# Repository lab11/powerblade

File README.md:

PowerBlade
==========

PowerBlade is a miniature plug load power meter - it is small enough to fit
between the plug and the outlet while performing its metering operation.
Achieving this form factor requires targeting every aspect of traditional power
meters, including contact method, power supply, voltage and current sensing, and
data communication (Bluetooth Low Energy, in this case).

There have been multiple iterations of PowerBlade, starting with a backscatter-
based variant and eventually transitioning to the BLE version. Along the way
there have been several iterations of the contact method, starting with flexible
PCB layers to touch the prongs and ending with spring-loaded pins which make
contact more reliably and repeatably.

Future work on this system will include improvements to the accuracy of the unit
(PowerBlade readings currently have 5% to 10% error but we believe this can be
significantly lower), as well as safety.

How Do I View My PowerBlade's Data?
-----------------------------------

- **Option 1**: Install [Summon](https://github.com/lab11/summon)
[[Android](https://play.google.com/store/apps/details?id=edu.umich.eecs.lab11.summon&hl=en),
[iOS](https://itunes.apple.com/us/app/summon-lab11/id1051205682?mt=8)].

- **Option 2**: Run a node.js script to view packets on your computer.

    ```sh
    cd data_collection/advertisements/
    npm install
    sudo node powerblade_adv.js
    ```

    This requires that you have support for running as a BLE
    master on your machine. To get setup, see the instructions below.

### BLE and node.js Setup

1. Install [Node.js](https://nodejs.org/en/download/package-manager/) for your platform.
Node.js provides a JavaScript runtime to execute the data collection script in.

2. Install BLE dependencies for your platform.

    - **OS X**: Install [Xcode](https://itunes.apple.com/ca/app/xcode/id497799835?mt=12)
    - **Ubuntu/Debian/Raspbian**:

        ```sh
        sudo apt install bluetooth bluez libbluetooth-dev libudev-dev
        ```

    - **Fedora / Other-RPM based**:

        ```sh
        sudo yum install bluez bluez-libs bluez-libs-devel
        ```

    - **Intel Edison**: See [Configure Intel Edison for Bluetooth LE (Smart) Development](http://rexstjohn.com/configure-intel-edison-for-bluetooth-le-smart-development/)

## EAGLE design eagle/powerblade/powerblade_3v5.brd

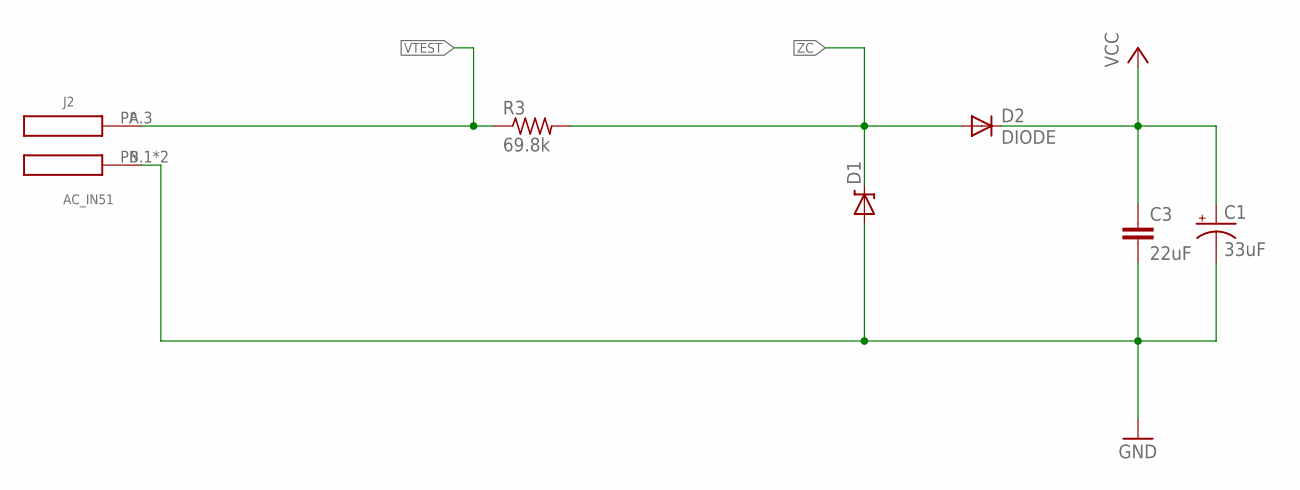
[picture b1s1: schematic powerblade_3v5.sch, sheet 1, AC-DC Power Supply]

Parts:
C1: 33uF; CPOL0805_SM; DIGIKEY 478-8650-1-ND
C3: 22uF; C0603_SM; DIGIKEY 445-9077-1-ND
D1: ZENERBZT52; BZT52; DIGIKEY BZT52C10T-7DICT-ND
D2: DIODE; BAS521
J2: AC_IN51; AC3_51; DIGIKEY ED1649-ND
R3: 69.8k; R1210; DIGIKEY P69.8KAACT-ND

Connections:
GND: C1.-, C3.2, D1.A, J2.PB.1 (N), J2.PB.3 (N); also elsewhere on the board
VCC: C1.+, C3.1, D2.C; also elsewhere on the board
VTEST: J2.PA.3, R3.1; also elsewhere on the board
ZC: D1.C, D2.A, R3.2; also elsewhere on the board

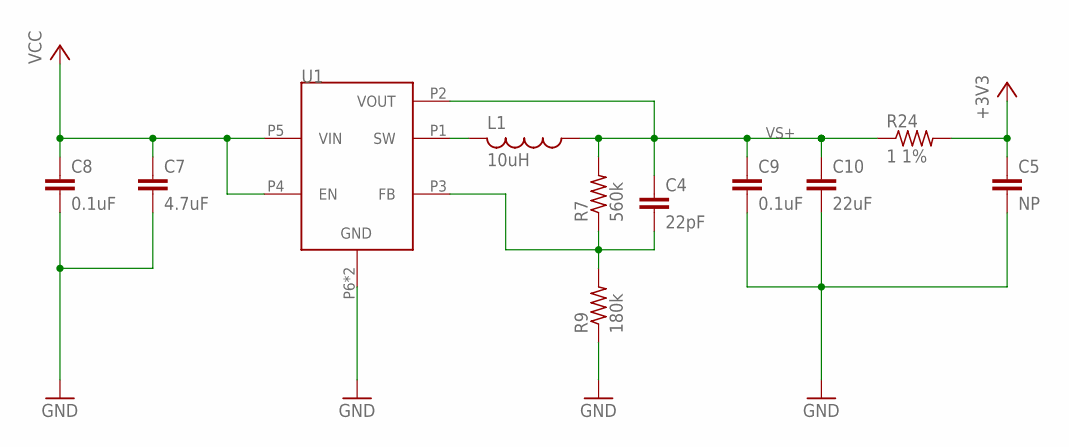
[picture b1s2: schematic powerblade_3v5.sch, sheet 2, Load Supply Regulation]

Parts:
C4: 22pF; C0402; DIGIKEY 445-1239-1-ND
C5: NP; C0603_TN; DIGIKEY NP
C7: 4.7uF; C0402; DIGIKEY 445-8023-1-ND
C8: 0.1uF; C0402; DIGIKEY 445-4952-1-ND
C9: 0.1uF; C0402_SM; DIGIKEY 445-4952-1-ND
C10: 22uF; C0603_SM; DIGIKEY 445-9077-1-ND
L1: 10uH; L0805; DIGIKEY 490-4990-1-ND
R7: 560k; R0402; DIGIKEY P560KLCT-ND
R9: 180k; R0402; DIGIKEY P180KLCT-ND
R24: 1 1%; R0603_SM; DIGIKEY P1.0AJCT-ND
U1: TPS62122; WDFN-6

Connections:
+3V3: C5.1, R24.2; also elsewhere on the board
GND: C5.2, C7.2, C8.2, C9.2, C10.2, R9.1, U1.P6 (GND), U1.PAD (GND); also elsewhere on the board
unnamed: L1.2, U1.P1 (SW)
unnamed: C4.2, R7.1, R9.2, U1.P3 (FB)
VCC: C7.1, C8.1, U1.P4 (EN), U1.P5 (VIN); also elsewhere on the board
VS+: C4.1, C9.1, C10.1, L1.1, R7.2, R24.1, U1.P2 (VOUT)

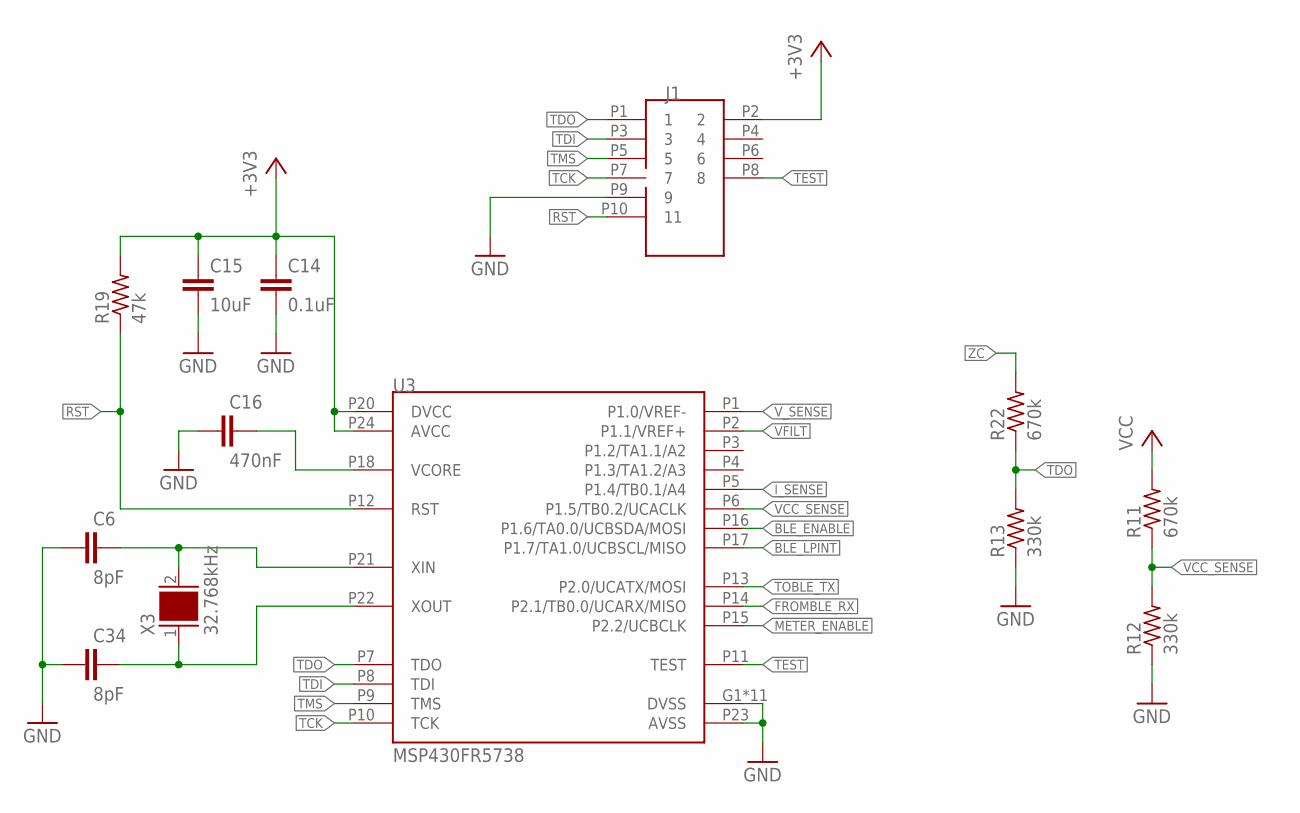
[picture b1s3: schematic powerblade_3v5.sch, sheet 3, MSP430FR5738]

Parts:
C6, C34: 8pF; C0402; DIGIKEY 445-4890-1-ND
C14: 0.1uF; C0402; DIGIKEY 445-4952-1-ND
C15: 10uF; C0603_SM; DIGIKEY 445-6853-1-ND
C16: 470nF; C0402; DIGIKEY 445-4989-1-ND
J1: JTAG_14PIN_IDC-ND; TC2050-IDC-NL-430-ND; DIGIKEY NP
R11, R22: 670k; R0402; DIGIKEY P665KLCT-ND
R12, R13: 330k; R0402; DIGIKEY P330KLCT-ND
R19: 47k; R0402; DIGIKEY P47KJCT-ND
U3: MSP430FR5738; VQFN-24
X3: 32.768kHz; 0805; DIGIKEY 535-12373-1-ND

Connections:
+3V3: C14.1, C15.1, J1.P2 (2), R19.2, U3.P20 (DVCC), U3.P24 (AVCC); also elsewhere on the board
BLE_ENABLE: U3.P16 (P1.6/TA0.0/UCBSDA/MOSI); also elsewhere on the board
BLE_LPINT: U3.P17 (P1.7/TA1.0/UCBSCL/MISO); also elsewhere on the board
FROMBLE_RX: U3.P14 (P2.1/TB0.0/UCARX/MISO); also elsewhere on the board
GND: C6.1, C14.2, C15.2, C16.1, C34.1, J1.P9 (9), R12.1, R13.1, U3.G1 (DVSS), U3.G2 (DVSS), U3.G3 (DVSS), U3.G4 (DVSS), U3.G5 (DVSS), U3.G6 (DVSS), U3.G7 (DVSS), U3.G8 (DVSS), U3.G9 (DVSS), U3.P19 (DVSS), U3.P23 (AVSS), U3.PAD (DVSS); also elsewhere on the board
I_SENSE: U3.P5 (P1.4/TB0.1/A4); also elsewhere on the board
METER_ENABLE: U3.P15 (P2.2/UCBCLK); also elsewhere on the board
unnamed: C34.2, U3.P22 (XOUT), X3.1
unnamed: C16.2, U3.P18 (VCORE)
unnamed: C6.2, U3.P21 (XIN), X3.2
RST: J1.P10 (11), R19.1, U3.P12 (RST)
TCK: J1.P7 (7), U3.P10 (TCK)
TDI: J1.P3 (3), U3.P8 (TDI)
TDO: J1.P1 (1), R13.2, R22.1, U3.P7 (TDO)
TEST: J1.P8 (8), U3.P11 (TEST)
TMS: J1.P5 (5), U3.P9 (TMS)
TOBLE_TX: U3.P13 (P2.0/UCATX/MOSI); also elsewhere on the board
VCC: R11.2; also elsewhere on the board
VCC_SENSE: R11.1, R12.2, U3.P6 (P1.5/TB0.2/UCACLK)
VFILT: U3.P2 (P1.1/VREF+); also elsewhere on the board
V_SENSE: U3.P1 (P1.0/VREF-); also elsewhere on the board
ZC: R22.2; also elsewhere on the board

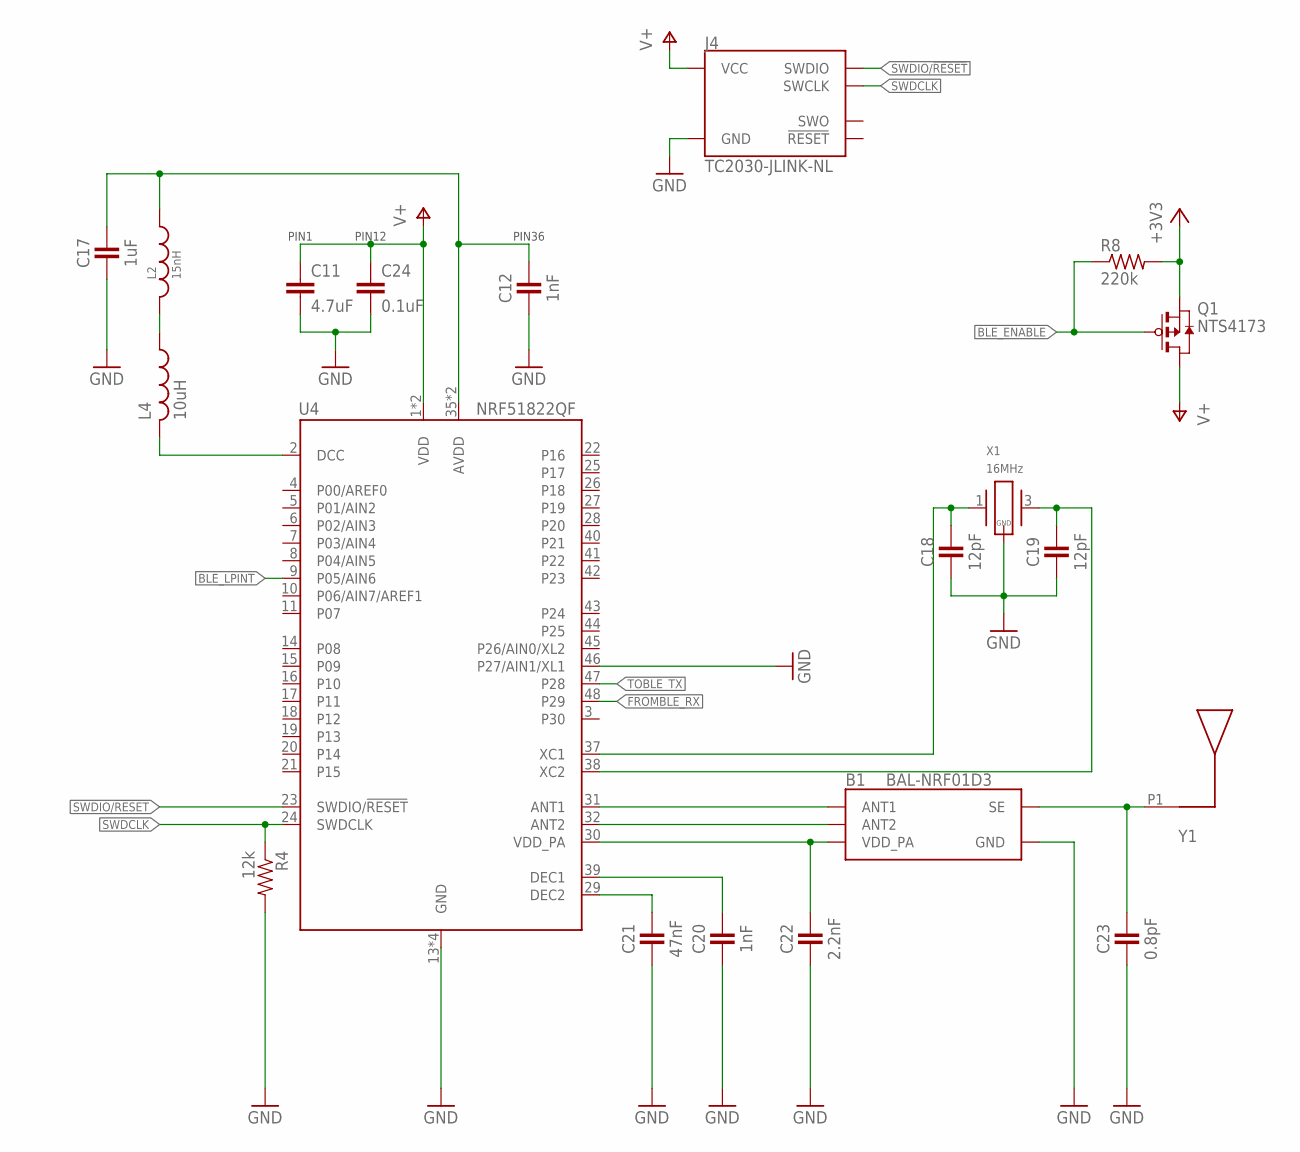
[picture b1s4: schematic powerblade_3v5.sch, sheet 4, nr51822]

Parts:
B1: BAL-NRF01D3
C11: 4.7uF; C0402; DIGIKEY 445-5947-1-ND
C12, C20: 1nF; 0402_CAP; DIGIKEY 490-1303-1-ND
C17: 1uF; 0402_CAP; DIGIKEY 1276-1513-1-ND
C18, C19: 12pF; 0402_CAP; DIGIKEY 490-6197-1-ND
C21: 47nF; 0402_CAP; DIGIKEY 445-1264-1-ND
C22: 2.2nF; 0402_CAP; DIGIKEY 490-5419-1-ND
C23: 0.8pF; 0402_CAP; DIGIKEY 490-6269-1-ND
C24: 0.1uF; C0402; DIGIKEY 445-4952-1-ND
J4: TC2030-JLINK-NL; TC2030-IDC-NL; DIGIKEY NP
L2: 15nH; 0402_CAP; DIGIKEY 587-1521-1-ND
L4: 10uH; C0603_TN; DIGIKEY 490-4025-1-ND
Q1: NTS4173; SC-70-3
R4: 12k; 0402_RES; DIGIKEY RHM12.0KCDCT-ND
R8: 220k; R0402_SM; DIGIKEY P220KJCT-ND
U4: NRF51822QF; QFN-48-6MM
X1: 16MHz; TXC-8Y; DIGIKEY 887-2003-1-ND
Y1: UREACH_XTEND

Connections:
+3V3: Q1.P2 (S), R8.2; also elsewhere on the board
AVDD: C12.1, C17.1, L2.1, U4.35 (AVDD), U4.36 (AVDD)
BLE_ENABLE: Q1.P1 (G), R8.1; also elsewhere on the board
BLE_LPINT: U4.9 (P05/AIN6); also elsewhere on the board
DCC: L4.2, U4.2 (DCC)
FROMBLE_RX: U4.48 (P29); also elsewhere on the board
GND: B1.GND, C11.2, C12.2, C17.2, C18.2, C19.2, C20.2, C21.2, C22.2, C23.2, C24.2, J4.5 (GND), R4.2, U4.13 (GND), U4.33 (GND), U4.34 (GND), U4.46 (P27/AIN1/XL1), U4.GND, X1.2 (GND), X1.4 (GND); also elsewhere on the board
unnamed: B1.SE, C23.1, Y1.P1
unnamed: B1.ANT1, U4.31 (ANT1)
unnamed: B1.ANT2, U4.32 (ANT2)
unnamed: L2.2, L4.1
unnamed: C18.1, U4.37 (XC1), X1.1
unnamed: C19.1, U4.38 (XC2), X1.3 (2)
unnamed: C20.1, U4.39 (DEC1)
unnamed: C21.1, U4.29 (DEC2)
SWDCLK: J4.4 (SWCLK), R4.1, U4.24 (SWDCLK)
SWDIO/!RESET: J4.2 (SWDIO), U4.23 (SWDIO/!RESET)
TOBLE_TX: U4.47 (P28); also elsewhere on the board
V+: C11.1, C24.1, J4.1 (VCC), Q1.P3 (D), U4.1 (VDD), U4.12 (VDD)
VDD_PA: B1.VCC (VDD_PA), C22.1, U4.30 (VDD_PA)

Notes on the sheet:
PIN12
PIN1
PIN36

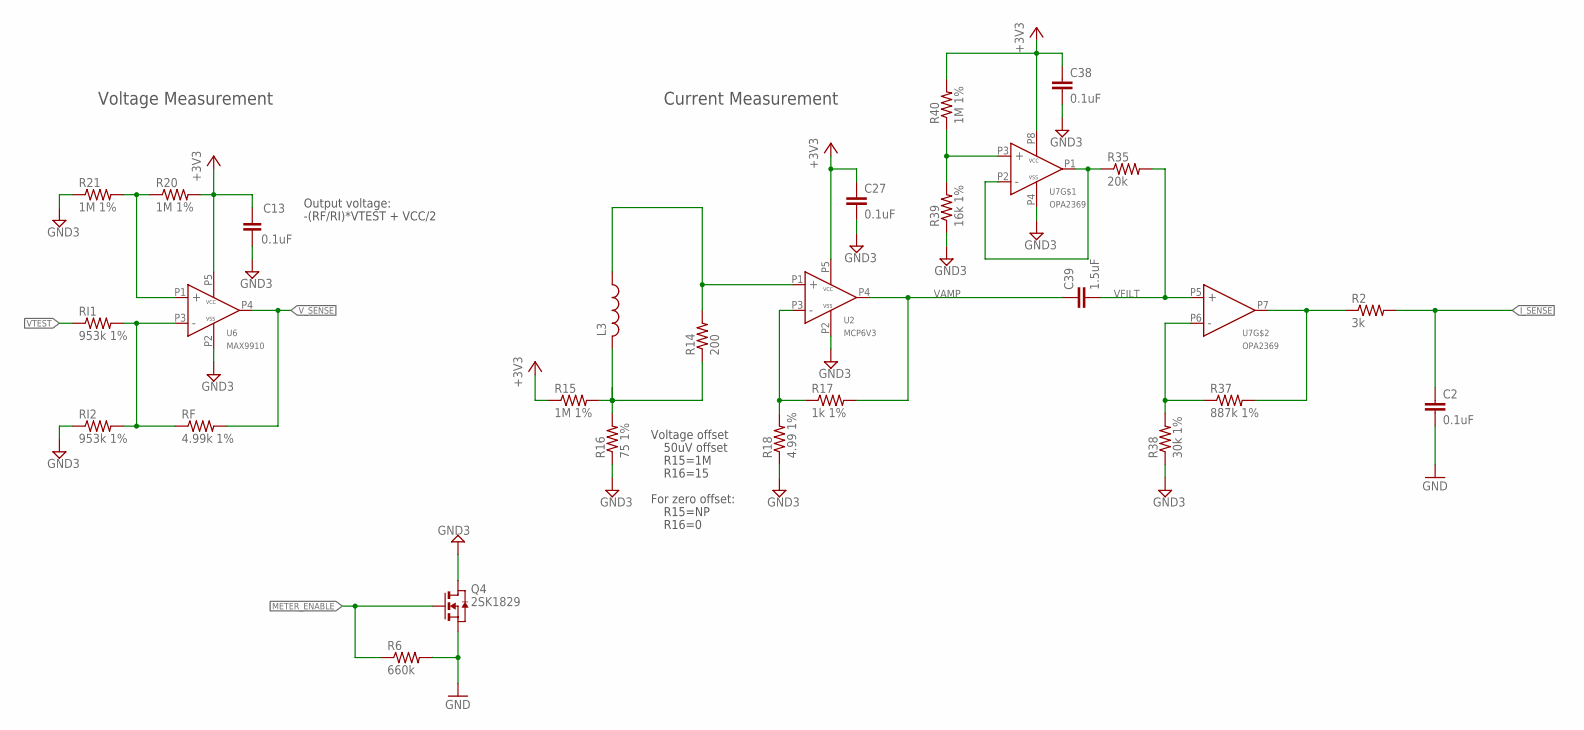
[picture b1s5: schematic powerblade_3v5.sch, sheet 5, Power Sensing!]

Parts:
C2: 0.1uF; C0402; DIGIKEY 490-10777-1-ND
C13: 0.1uF; 0402_CAP; DIGIKEY 445-4952-1-ND
C27, C38: 0.1uF; C0402; DIGIKEY 445-4952-1-ND
C39: 1.5uF; C0402; DIGIKEY 445-13815-1-ND
L3: L-USL0805; L0805; DIGIKEY 732-3452-1-ND
Q4: 2SK1829; SC-70-3
R2: 3k; R0402_SM; DIGIKEY P3.00KLCT-ND
R6: 660k; R0402; DIGIKEY P665KLCT-ND
R14: 200; R0402; DIGIKEY P200LCT-ND
R15, R20, R40: 1M 1%; R0402; DIGIKEY P1.00MLCT-ND
R16: 75 1%; R0402; DIGIKEY P75.0LCT-ND
R17: 1k 1%; R0402; DIGIKEY P1.00KLCT-ND
R18: 4.99 1%; R0402; DIGIKEY RMCF0402FT4R99CT-ND
R21: 1M 1%; R0402_SM; DIGIKEY P1.00MLCT-ND
R35: 20k; R0402; DIGIKEY P20.0KLCT-ND
R37: 887k 1%; R0402; DIGIKEY P887KLCT-ND
R38: 30k 1%; R0402; DIGIKEY P30.0KLCT-ND
R39: 16k 1%; R0402; DIGIKEY P16.0KLCT-ND
RF: 4.99k 1%; R0402; DIGIKEY P4.99KLCT-ND
RI1, RI2: 953k 1%; R0402; DIGIKEY P953KLCT-ND
U2: MCP6V3; SC70-5; DIGIKEY 296-19547-1-ND
U6: MAX9910; SC70-5; DIGIKEY 296-25252-1-ND
U7: OPA2369; SOT-23-8

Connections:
+3V3: C13.1, C27.1, C38.1, R15.1, R20.2, R40.2, U2.P5 (VCC), U6.P5 (VCC), U7.P8 (VCC); also elsewhere on the board
GND: C2.2, Q4.P2 (S), R6.2; also elsewhere on the board
GND3: C13.2, C27.2, C38.2, Q4.P3 (D), R16.1, R18.1, R21.1, R38.1, R39.1, RI2.1, U2.P2 (VSS), U6.P2 (VSS), U7.P4 (VSS)
I_SENSE: C2.1, R2.2; also elsewhere on the board
METER_ENABLE: Q4.P1 (G), R6.1; also elsewhere on the board
unnamed: R2.1, R37.2, U7.P7 (OUT)
unnamed: L3.2, R14.1, R15.2, R16.2
unnamed: L3.1, R14.2, U2.P1 (IN+)
unnamed: R20.1, R21.2, U6.P1 (IN+)
unnamed: RF.1, RI1.2, RI2.2, U6.P3 (IN-)
unnamed: R17.1, R18.2, U2.P3 (IN-)
unnamed: R37.1, R38.2, U7.P6 (IN-)
unnamed: R35.1, U7.P1 (OUT), U7.P2 (IN-)
unnamed: R39.2, R40.1, U7.P3 (IN+)
VAMP: C39.1, R17.2, U2.P4 (OUT)
VFILT: C39.2, R35.2, U7.P5 (IN+); also elsewhere on the board
VTEST: RI1.1; also elsewhere on the board
V_SENSE: RF.2, U6.P4 (OUT); also elsewhere on the board

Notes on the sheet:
Voltage offset
50uV offset
For zero offset:
R15=NP
R16=0
Current Measurement
Voltage Measurement
Output voltage:
-(RF/RI)*VTEST + VCC/2
R15=1M
R16=15

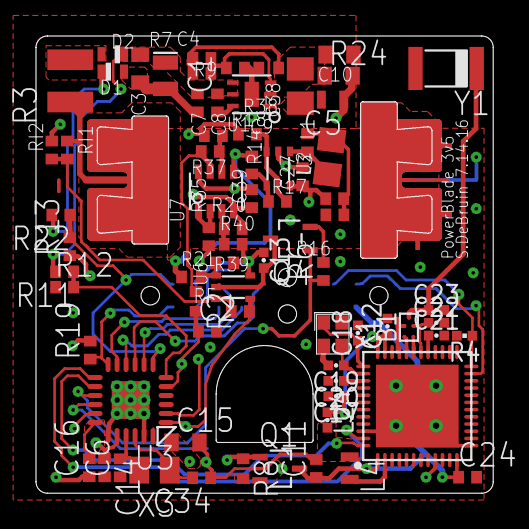
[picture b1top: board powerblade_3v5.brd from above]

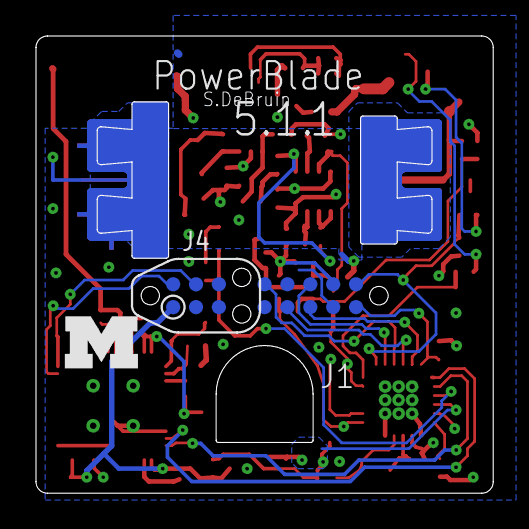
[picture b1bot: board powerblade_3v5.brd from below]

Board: 4 copper layers, 25.4 x 25.4 mm, 78 parts (3 on the bottom side), 51 nets.

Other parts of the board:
U$1: BLOCK-M

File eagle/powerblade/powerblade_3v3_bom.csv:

"Part";"Value";"Device";"Package";"Description";"DIGIKEY";"DIGIKEY_2";"DIGIKEY_3";"DIGIKEY_4";"FRACTUS";"MOUSER";
"B1";"BAL-NRF01D3";"BAL-NRF01D3";"BAL-NRF01D3";"50 ohm nominal input / conjugate match balun to nRF51422-QFAA,";"497-13637-1-ND";"";"";"";"";"511-BAL-NRF01D3";
"C1";"33uF";"CPOL-US0805_SM";"CPOL0805_SM";"POLARIZED CAPACITOR, American symbol";"478-8650-1-ND";"";"";"";"";"";
"C2";"0.1uF";"C-EUC0402";"C0402";"CAPACITOR, European symbol";"490-10777-1-ND";"";"";"";"";"";
"C3";"22uF";"C-EUC0603_SM";"C0603_SM";"CAPACITOR, European symbol";"445-9077-1-ND";"";"";"";"";"";
"C4";"22pF";"C-EUC0402";"C0402";"CAPACITOR, European symbol";"445-1239-1-ND";"";"";"";"";"";
"C5";"NP";"C-EUC0603_TN";"C0603_TN";"CAPACITOR, European symbol";"NP";"";"";"";"";"";
"C6";"8pF";"C-EUC0402";"C0402";"CAPACITOR, European symbol";"445-4890-1-ND";"";"";"";"";"";
"C7";"4.7uF";"C-EUC0402";"C0402";"CAPACITOR, European symbol";"445-8023-1-ND";"";"";"";"";"";
"C8";"0.1uF";"C-EUC0402";"C0402";"CAPACITOR, European symbol";"445-4952-1-ND";"";"";"";"";"";
"C9";"0.1uF";"C-EUC0402_SM";"C0402_SM";"CAPACITOR, European symbol";"445-4952-1-ND";"";"";"";"";"";
"C10";"22uF";"C-EUC0603_SM";"C0603_SM";"CAPACITOR, European symbol";"445-9077-1-ND";"";"";"";"";"";
"C11";"4.7uF";"C-EUC0402";"C0402";"CAPACITOR, European symbol";"445-5947-1-ND";"";"";"";"";"";
"C12";"1nF";"CAPACITOR";"0402_CAP";"0402 Capacitor";"490-1303-1-ND";"";"";"";"";"";
"C13";"0.1uF";"CAPACITOR";"0402_CAP";"0402 Capacitor";"445-4952-1-ND";"";"";"";"";"";
"C14";"0.1uF";"C-EUC0402";"C0402";"CAPACITOR, European symbol";"445-4952-1-ND";"";"";"";"";"";
"C15";"10uF";"C-EUC0603_SM";"C0603_SM";"CAPACITOR, European symbol";"445-6853-1-ND";"";"";"";"";"";
"C16";"470nF";"C-EUC0402";"C0402";"CAPACITOR, European symbol";"445-4989-1-ND";"";"";"";"";"";
"C17";"1uF";"CAPACITOR";"0402_CAP";"0402 Capacitor";"1276-1513-1-ND";"";"";"";"";"";
"C18";"12pF";"CAPACITOR";"0402_CAP";"0402 Capacitor";"490-6197-1-ND";"";"";"";"";"";
"C19";"12pF";"CAPACITOR";"0402_CAP";"0402 Capacitor";"490-6197-1-ND";"";"";"";"";"";
"C20";"1nF";"CAPACITOR";"0402_CAP";"0402 Capacitor";"490-1303-1-ND";"";"";"";"";"";
"C21";"47nF";"CAPACITOR";"0402_CAP";"0402 Capacitor";"445-1264-1-ND";"";"";"";"";"";
"C22";"2.2nF";"CAPACITOR";"0402_CAP";"0402 Capacitor";"490-5419-1-ND";"";"";"";"";"";
"C23";"0.8pF";"CAPACITOR";"0402_CAP";"0402 Capacitor";"490-6269-1-ND";"";"";"";"";"";
"C24";"0.1uF";"C-EUC0402";"C0402";"CAPACITOR, European symbol";"445-4952-1-ND";"";"";"";"";"";
"C27";"0.1uF";"C-EUC0402";"C0402";"CAPACITOR, European symbol";"445-4952-1-ND";"";"";"";"";"";
"C34";"8pF";"C-EUC0402";"C0402";"CAPACITOR, European symbol";"445-4890-1-ND";"";"";"";"";"";
"C38";"0.1uF";"C-EUC0402";"C0402";"CAPACITOR, European symbol";"445-4952-1-ND";"";"";"";"";"";
"C39";"1.5uF";"C-EUC0402";"C0402";"CAPACITOR, European symbol";"445-13815-1-ND";"";"";"";"";"";
"D1";"ZENERBZT52";"ZENERBZT52";"BZT52";"";"BZT52C10T-7DICT-ND ";"";"";"";"";"";
"D2";"DIODE";"DIODE";"BAS521";"";"BAS521-7DICT-ND";"";"";"";"";"";
"J1";"JTAG_14PIN_IDC-ND";"JTAG_14PIN_IDC-ND";"TC2050-IDC-NL-430-ND";"";"NP";"";"";"";"";"";
"J2";"AC_INF45";"AC_INF45";"AC3_F45";"";"ED1649-ND";"ED1649-ND";"ED1649-ND";"ED1649-ND";"";"";
"J4";"TC2030-JLINK-NL";"TC2030-JLINK-NL";"TC2030-IDC-NL";"";"NP";"";"";"";"";"";
"L1";"10uH";"L-USL0805";"L0805";"INDUCTOR, American symbol";"490-4990-1-ND";"";"";"";"";"";
"L2";"15nH";"INDUCTOR0402";"0402_CAP";"";"587-1521-1-ND";"";"";"";"";"";
"L3";"";"L-USL0805";"L0805";"INDUCTOR, American symbol";"732-3452-1-ND";"";"";"";"";"";
"L4";"10uH";"L-USL0603_TN";"C0603_TN";"INDUCTOR, American symbol";"490-4025-1-ND";"";"";"";"";"";
"Q1";"NTS4173";"NTS4173";"SC-70-3";"";"NTS4173PT1GOSCT-ND";"";"";"";"";"";
"Q4";"2SK1829";"2SK1829";"SC-70-3";"";"2SK1829TE85LFCT-ND";"";"";"";"";"";
"R2";"3k";"R-US_R0402_SM";"R0402_SM";"RESISTOR, American symbol";"P3.00KLCT-ND";"";"";"";"";"";
"R3";"69.8k";"R-US_R1210";"R1210";"RESISTOR, American symbol";"P69.8KAACT-ND";"";"";"";"";"";
"R4";"12k";"RESISTOR";"0402_RES";"Resistor";"RHM12.0KCDCT-ND";"";"";"";"";"";
"R6";"660k";"R-US_R0402";"R0402";"RESISTOR, American symbol";"P665KLCT-ND";"";"";"";"";"";
"R7";"560k";"R-US_R0402";"R0402";"RESISTOR, American symbol";"P560KLCT-ND";"";"";"";"";"";
"R8";"220k";"R-US_R0402_SM";"R0402_SM";"RESISTOR, American symbol";"P220KJCT-ND";"";"";"";"";"";
"R9";"180k";"R-US_R0402";"R0402";"RESISTOR, American symbol";"P180KLCT-ND";"";"";"";"";"";
"R11";"670k";"R-US_R0402";"R0402";"RESISTOR, American symbol";"P665KLCT-ND";"";"";"";"";"";
"R12";"330k";"R-US_R0402";"R0402";"RESISTOR, American symbol";"P330KLCT-ND";"";"";"";"";"";
"R13";"330k";"R-US_R0402";"R0402";"RESISTOR, American symbol";"P330KLCT-ND";"";"";"";"";"";
"R14";"200";"R-US_R0402";"R0402";"RESISTOR, American symbol";"P200LCT-ND";"";"";"";"";"";
"R15";"1M 1%";"R-US_R0402";"R0402";"RESISTOR, American symbol";"P1.00MLCT-ND";"";"";"";"";"";
"R16";"75 1%";"R-US_R0402";"R0402";"RESISTOR, American symbol";"P75.0LCT-ND";"";"";"";"";"";
"R17";"1k 1%";"R-US_R0402";"R0402";"RESISTOR, American symbol";"P1.00KLCT-ND";"";"";"";"";"";
"R18";"4.99 1%";"R-US_R0402";"R0402";"RESISTOR, American symbol";"RMCF0402FT4R99CT-ND";"";"";"";"";"";
"R19";"47k";"R-US_R0402";"R0402";"RESISTOR, American symbol";"P47KJCT-ND";"";"";"";"";"";
"R20";"1M 1%";"R-US_R0402";"R0402";"RESISTOR, American symbol";"P1.00MLCT-ND";"";"";"";"";"";
"R21";"1M 1%";"R-US_R0402_SM";"R0402_SM";"RESISTOR, American symbol";"P1.00MLCT-ND";"";"";"";"";"";
"R22";"670k";"R-US_R0402";"R0402";"RESISTOR, American symbol";"P665KLCT-ND";"";"";"";"";"";
"R24";"1 1%";"R-US_R0603_SM";"R0603_SM";"RESISTOR, American symbol";"P1.0AJCT-ND";"";"";"";"";"";
"R35";"20k";"R-US_R0402";"R0402";"RESISTOR, American symbol";"P20.0KLCT-ND";"";"";"";"";"";
"R37";"887k 1%";"R-US_R0402";"R0402";"RESISTOR, American symbol";"P887KLCT-ND";"";"";"";"";"";
"R38";"30k 1%";"R-US_R0402";"R0402";"RESISTOR, American symbol";"P30.0KLCT-ND";"";"";"";"";"";
"R39";"16k 1%";"R-US_R0402";"R0402";"RESISTOR, American symbol";"P16.0KLCT-ND";"";"";"";"";"";
"R40";"1M 1%";"R-US_R0402";"R0402";"RESISTOR, American symbol";"P1.00MLCT-ND";"";"";"";"";"";
"RF";"4.99k 1%";"R-US_R0402";"R0402";"RESISTOR, American symbol";"P4.99KLCT-ND";"";"";"";"";"";
"RI1";"953k 1%";"R-US_R0402";"R0402";"RESISTOR, American symbol";"P953KLCT-ND";"";"";"";"";"";
"RI2";"953k 1%";"R-US_R0402";"R0402";"RESISTOR, American symbol";"P953KLCT-ND";"";"";"";"";"";
"SV1";"";"MA12-11M27";"MA12-1_1MM27";"PIN HEADER";"S9014E-12-ND";"";"";"";"";"";
"U1";"TPS62122";"TPS62122";"WDFN-6";"";"296-27695-1-ND";"";"";"";"";"";
"U2";"MCP6V3";"MCP6V3";"SC70-5";"";"296-19547-1-ND";"";"";"";"";"";
"U3";"MSP430FR5738";"MSP430FR5738";"VQFN-24";"";"296-29232-1-ND";"";"";"";"";"";
"U4";"NRF51822QF";"NRF51822QF";"QFN-48-6MM";"Multiprotocol Bluetooth® 4.0 low energy/2.4 GHz RF SoC";"1490-1032-1-ND";"";"";"";"";"949-NRF51822-QFAB-R7";
"U6";"MAX9910";"MAX9910";"SC70-5";"";"296-25252-1-ND";"";"";"";"";"";
"U7";"OPA2369";"OPA2369";"SOT-23-8";"";"296-22671-1-ND";"";"";"";"";"";
"X1";"16MHz";"TXC-8Y";"TXC-8Y";"2mmx1.6mm SMD Crystal";"887-2003-1-ND";"";"";"";"";"";
"X3";"32.768kHz";"CRYSTAL_0805";"0805";"";"535-12373-1-ND";"";"";"";"";"";
"Y1";"UREACH_XTEND";"UREACH_XTEND";"UREACH_XTEND";"";"";"";"";"";"FR05-S1-N-0-110";"";

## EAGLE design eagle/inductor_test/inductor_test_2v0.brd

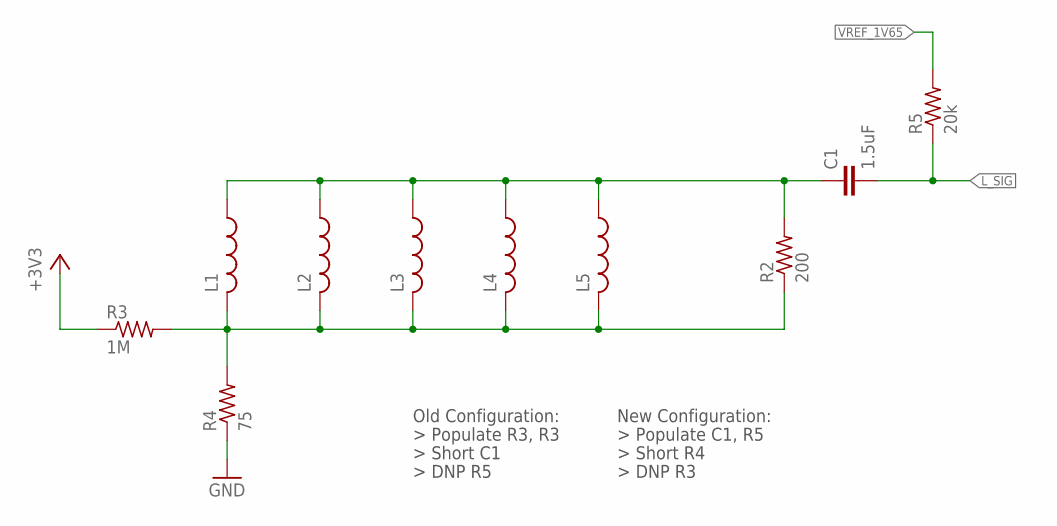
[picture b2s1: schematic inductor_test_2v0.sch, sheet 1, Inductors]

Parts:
C1: 1.5uF; C0402; DIGIKEY 445-13815-1-ND
L1, L2, L3, L4, L5: L-USL0805; L0805; DIGIKEY 732-3452-1-ND
R2: 200; R0402; DIGIKEY P200LCT-ND
R3: 1M; R0402; DIGIKEY P1.00MLCT-ND
R4: 75; R0402; DIGIKEY P75.0LCT-ND
R5: 20k; R0402; DIGIKEY P20.0KLCT-ND

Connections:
+3V3: R3.1; also elsewhere on the board
GND: R4.1; also elsewhere on the board
L1P2: L1.2, L2.2, L3.2, L4.2, L5.2, R2.1, R3.2, R4.2
L_SIG: C1.2, R5.1; also elsewhere on the board
unnamed: C1.1, L1.1, L2.1, L3.1, L4.1, L5.1, R2.2
VREF_1V65: R5.2; also elsewhere on the board

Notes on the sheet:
Old Configuration:
New Configuration:

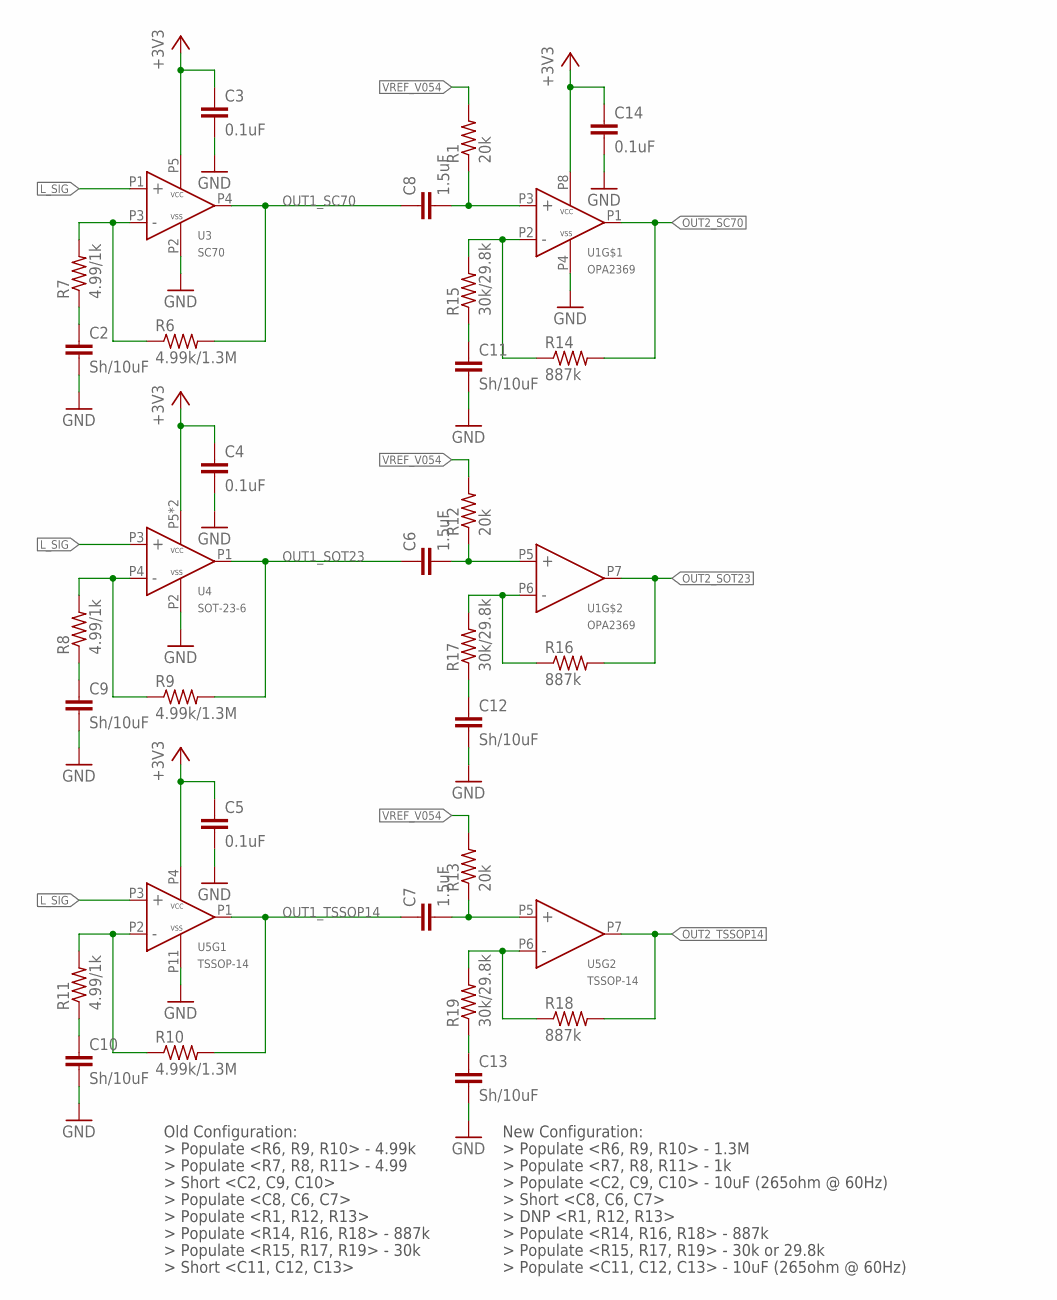
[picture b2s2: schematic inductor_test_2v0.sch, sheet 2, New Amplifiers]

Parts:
C2, C9, C10, C11, C12, C13: Sh/10uF; C0402; DIGIKEY 1276-1450-1-ND
C3, C4, C5, C14: 0.1uF; C0402; DIGIKEY 445-4952-1-ND
C6, C7, C8: 1.5uF; C0402; DIGIKEY 445-13815-1-ND
R1, R12, R13: 20k; R0402; DIGIKEY P20.0KLCT-ND
R6, R9, R10: 4.99k/1.3M; R0402; DIGIKEY P4.99KLCT-ND
R7, R8, R11: 4.99/1k; R0402; DIGIKEY RMCF0402FT4R99CT-ND
R14, R16, R18: 887k; R0402; DIGIKEY P887KLCT-ND
R15, R17, R19: 30k/29.8k; R0402; DIGIKEY P30.0KLCT-ND
U1: OPA2369; SOT-23-8
U3: SC70; SC70-5; DIGIKEY 296-22191-1-ND
U4: SOT-23-6
U5: TSSOP-14

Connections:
+3V3: C3.1, C4.1, C5.1, C14.1, U1.P8 (VCC), U3.P5 (VCC), U4.P5 (VCC), U4.P6 (VCC), U5.P4 (VCC); also elsewhere on the board
GND: C2.2, C3.2, C4.2, C5.2, C9.2, C10.2, C11.2, C12.2, C13.2, C14.2, U1.P4 (VSS), U3.P2 (VSS), U4.P2 (VSS), U5.P11 (VSS); also elsewhere on the board
L_SIG: U3.P1 (IN+), U4.P3 (IN+), U5.P3 (IN+); also elsewhere on the board
unnamed: C10.1, R11.1
unnamed: C9.1, R8.1
unnamed: R6.1, R7.2, U3.P3 (IN-)
unnamed: R8.2, R9.1, U4.P4 (IN-)
unnamed: C2.1, R7.1
unnamed: C8.2, R1.1, U1.P3 (IN+)
unnamed: R10.1, R11.2, U5.P2 (IN-)
unnamed: R14.1, R15.2, U1.P2 (IN-)
unnamed: C6.2, R12.1, U1.P5 (IN+)
unnamed: C11.1, R15.1
unnamed: C7.2, R13.1, U5.P5 (IN+)
unnamed: R16.1, R17.2, U1.P6 (IN-)
unnamed: C12.1, R17.1
unnamed: R18.1, R19.2, U5.P6 (IN-)
unnamed: C13.1, R19.1
OUT1_SC70: C8.1, R6.2, U3.P4 (OUT); also elsewhere on the board
OUT1_SOT23: C6.1, R9.2, U4.P1 (OUT); also elsewhere on the board
OUT1_TSSOP14: C7.1, R10.2, U5.P1 (OUT); also elsewhere on the board
OUT2_SC70: R14.2, U1.P1 (OUT); also elsewhere on the board
OUT2_SOT23: R16.2, U1.P7 (OUT); also elsewhere on the board
OUT2_TSSOP14: R18.2, U5.P7 (OUT); also elsewhere on the board
VREF_V054: R1.2, R12.2, R13.2; also elsewhere on the board

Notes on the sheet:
Old Configuration:
New Configuration:

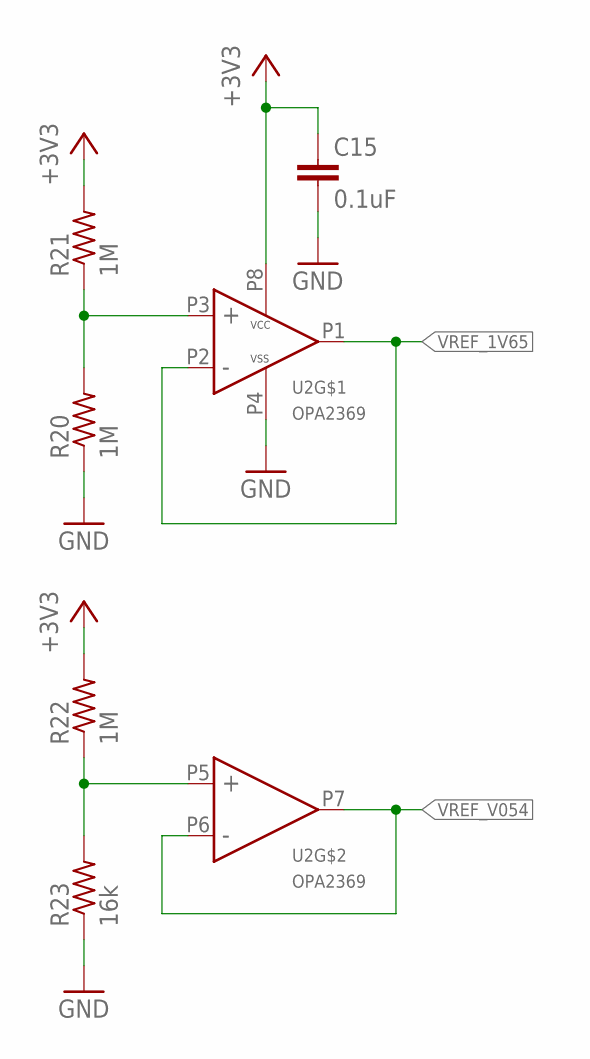
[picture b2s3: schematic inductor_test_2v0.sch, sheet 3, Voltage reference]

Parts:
C15: 0.1uF; C0402; DIGIKEY 445-4952-1-ND
R20, R21, R22: 1M; R0402; DIGIKEY P1.00MLCT-ND
R23: 16k; R0402; DIGIKEY P16.0KLCT-ND
U2: OPA2369; SOT-23-8

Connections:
+3V3: C15.1, R21.2, R22.2, U2.P8 (VCC); also elsewhere on the board
GND: C15.2, R20.1, R23.1, U2.P4 (VSS); also elsewhere on the board
unnamed: R22.1, R23.2, U2.P5 (IN+)
unnamed: R20.2, R21.1, U2.P3 (IN+)
VREF_1V65: U2.P1 (OUT), U2.P2 (IN-); also elsewhere on the board
VREF_V054: U2.P6 (IN-), U2.P7 (OUT); also elsewhere on the board

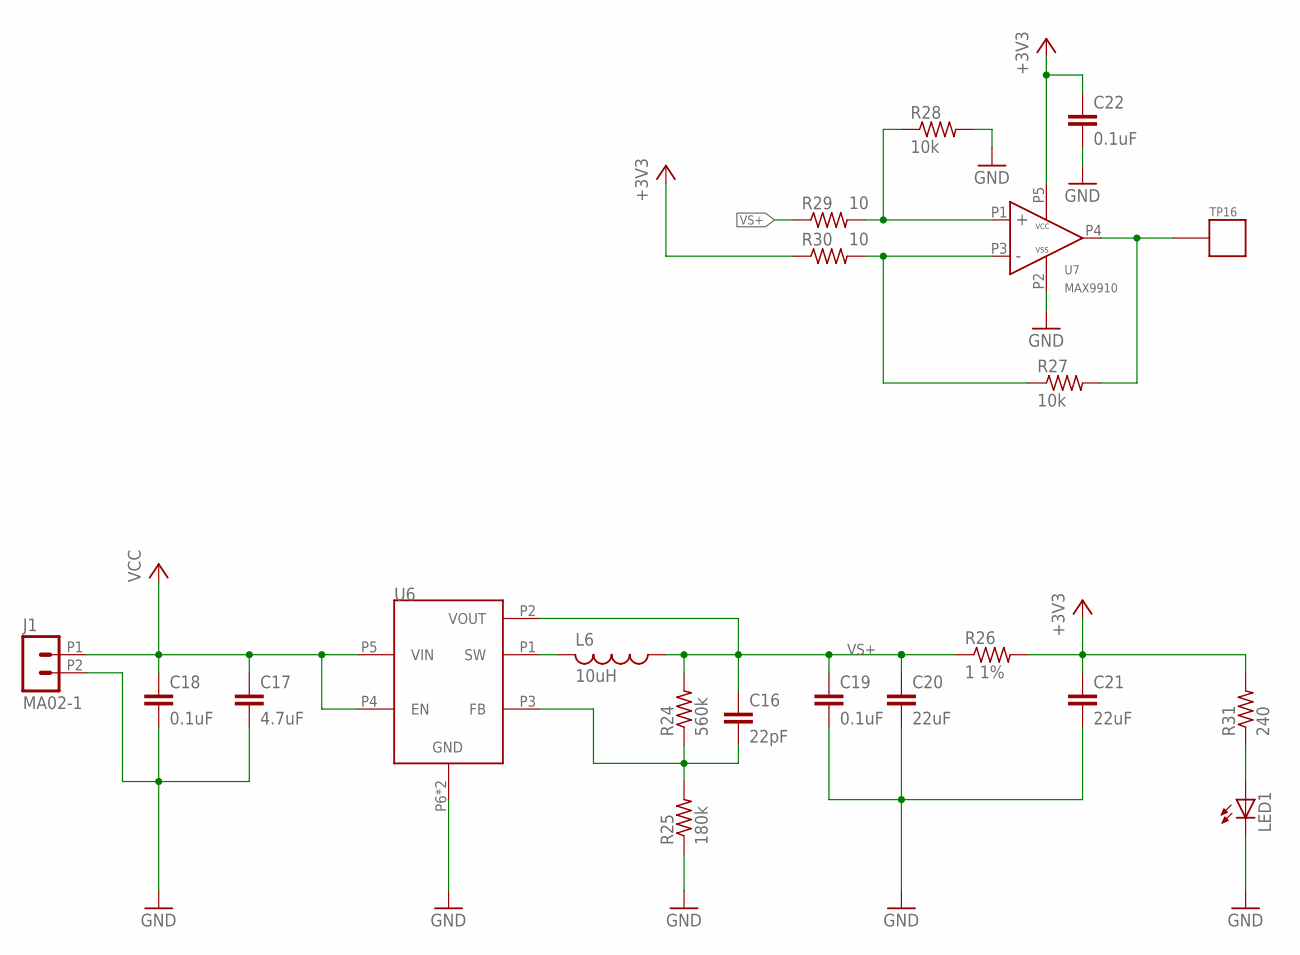
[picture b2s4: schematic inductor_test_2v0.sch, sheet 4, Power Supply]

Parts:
C16: 22pF; C0402_SM; DIGIKEY 445-1239-1-ND
C17: 4.7uF; C0402_SM; DIGIKEY 445-8023-1-ND
C18, C19: 0.1uF; C0402_SM; DIGIKEY 445-4952-1-ND
C20, C21: 22uF; C0603_SM; DIGIKEY 445-9077-1-ND
C22: 0.1uF; C0603; DIGIKEY 445-4952-1-ND
J1: MA02-1; MA02-1_MOLEX-TH
L6: 10uH; L0805; DIGIKEY 490-4990-1-ND
LED1: LED3MM; DIGIKEY 1125-1181-ND
R24: 560k; R0402_SM; DIGIKEY P560KLCT-ND
R25: 180k; R0402_SM; DIGIKEY P180KLCT-ND
R26: 1 1%; R0603_SM; DIGIKEY P1.0AJCT-ND
R27, R28: 10k; R0603; DIGIKEY P10KGCT-ND
R29, R30: 10; R0603; DIGIKEY P10GCT-ND
R31: 240; R0603; DIGIKEY P240GCT-ND
TP16: TP_MULT; DIGIKEY 36-5013-ND
U6: TPS62122; WDFN-6
U7: MAX9910; SC70-5

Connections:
+3V3: C21.1, C22.1, R26.2, R30.1, R31.2, U7.P5 (VCC); also elsewhere on the board
GND: C17.2, C18.2, C19.2, C20.2, C21.2, C22.2, J1.P2 (2), LED1.K (C), R25.1, R28.2, U6.P6 (GND), U6.PAD (GND), U7.P2 (VSS); also elsewhere on the board
unnamed: C16.2, R24.1, R25.2, U6.P3 (FB)
unnamed: L6.2, U6.P1 (SW)
unnamed: R28.1, R29.2, U7.P1 (IN+)
unnamed: R27.1, R30.2, U7.P3 (IN-)
unnamed: R27.2, TP16.P$1, U7.P4 (OUT)
unnamed: LED1.A, R31.1
VCC: C17.1, C18.1, J1.P1 (1), U6.P4 (EN), U6.P5 (VIN)
VS+: C16.1, C19.1, C20.1, L6.1, R24.2, R26.1, R29.1, U6.P2 (VOUT)

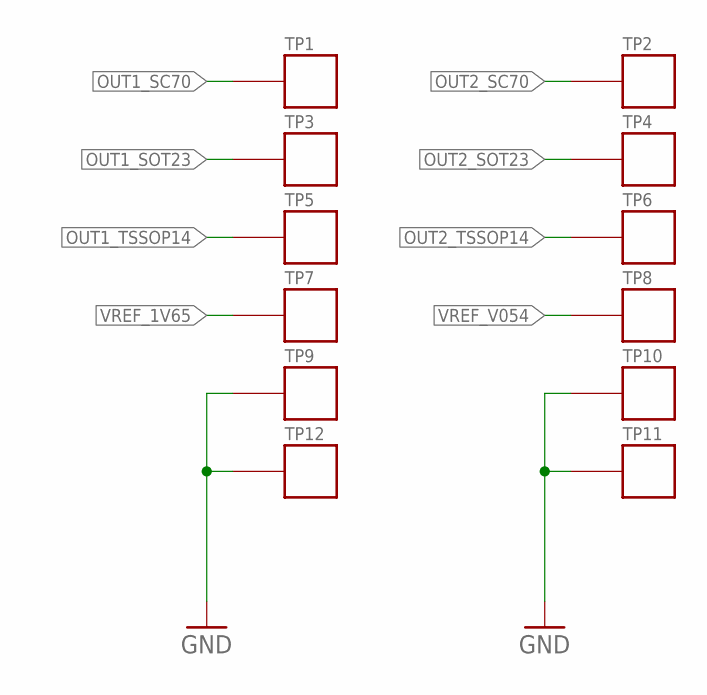
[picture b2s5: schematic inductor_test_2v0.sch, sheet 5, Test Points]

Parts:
TP1, TP2: TP_MULT; DIGIKEY 36-5126-ND
TP3, TP4: TP_MULT; DIGIKEY 36-5128-ND
TP5, TP6: TP_MULT; DIGIKEY 36-5014-ND
TP7, TP8: TP_MULT; DIGIKEY 36-5010-ND
TP9, TP10, TP11, TP12: TP_MULT; DIGIKEY 36-5011-ND

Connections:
GND: TP9.P$1, TP10.P$1, TP11.P$1, TP12.P$1; also elsewhere on the board
OUT1_SC70: TP1.P$1; also elsewhere on the board
OUT1_SOT23: TP3.P$1; also elsewhere on the board
OUT1_TSSOP14: TP5.P$1; also elsewhere on the board
OUT2_SC70: TP2.P$1; also elsewhere on the board
OUT2_SOT23: TP4.P$1; also elsewhere on the board
OUT2_TSSOP14: TP6.P$1; also elsewhere on the board
VREF_1V65: TP7.P$1; also elsewhere on the board
VREF_V054: TP8.P$1; also elsewhere on the board

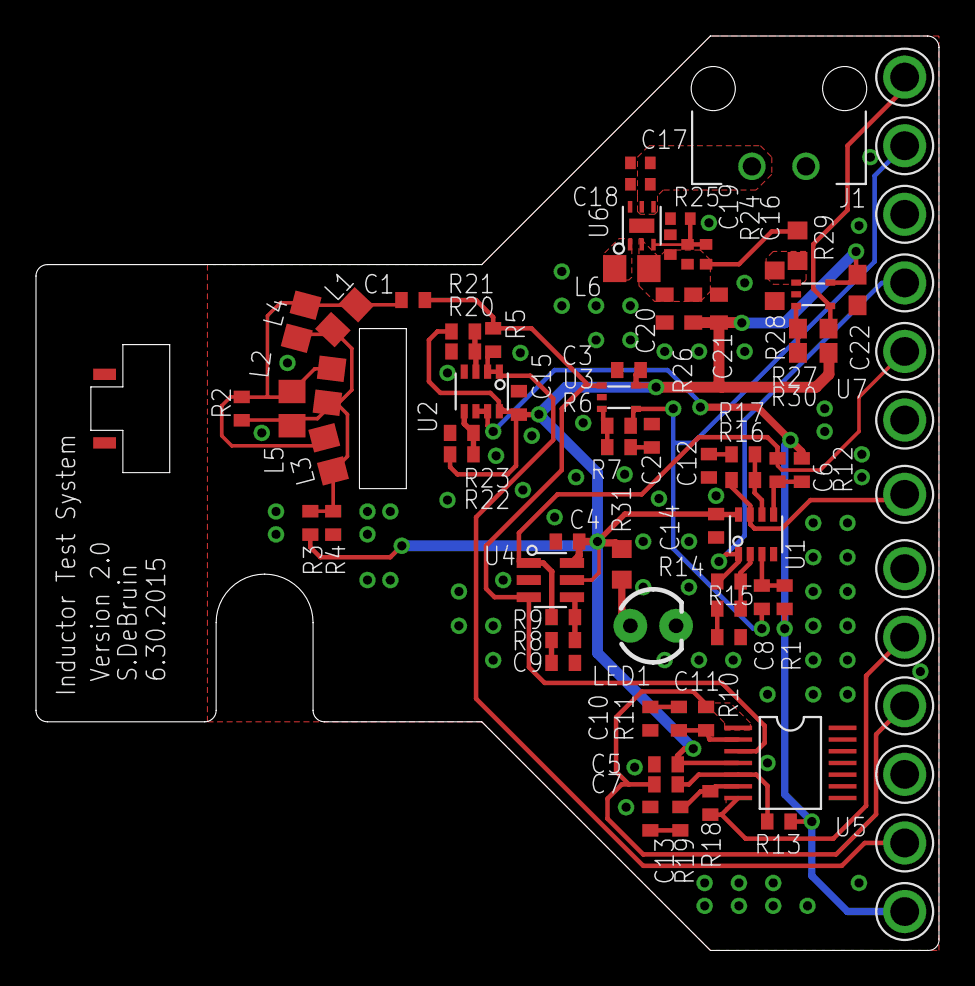
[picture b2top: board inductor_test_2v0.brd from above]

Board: 2 copper layers, 50.2 x 50.8 mm, 82 parts (0 on the bottom side), 38 nets.

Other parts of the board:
U$2: NEMA_F2

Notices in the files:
parts and their libraries:
SparkFun-LED: Licensing: CC v3.0 Share-Alike You are welcome to use this library for commercial purposes.
